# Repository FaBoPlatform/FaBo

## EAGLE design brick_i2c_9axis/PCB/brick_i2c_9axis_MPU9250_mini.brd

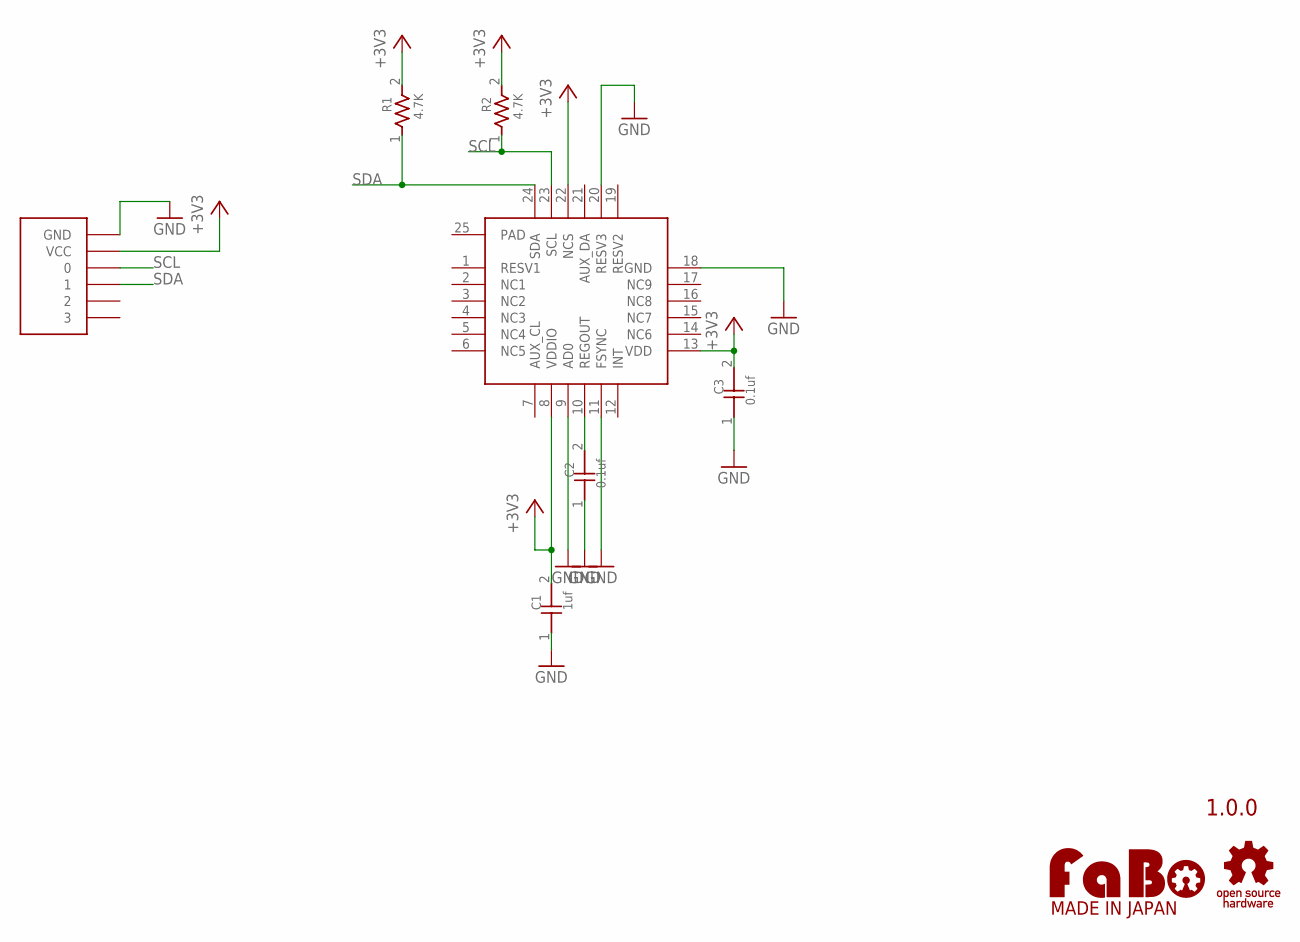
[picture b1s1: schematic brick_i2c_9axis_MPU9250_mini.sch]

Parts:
C1: 1uf; 0603
C2, C3: 0.1uf; 0603
R1, R2: 4.7K; 0603
U$1: INVENSENSE-MPU9250; LGA-24
U$3: LOGO_OSHW-S_BOTTOM; LOGO_OSHW_S_BOTTOM
U$4: FABO-NANO
U$5: LOGO_FABO-S_BOTTOM; LOGO_FABO_S_BOTTOM

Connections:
+3V3: C1.2, C3.2, R1.2, R2.2, U$1.8 (VDDIO), U$1.13 (VDD), U$1.22 (NCS), U$4.VCC
GND: C1.1, C2.1, C3.1, U$1.9 (AD0), U$1.11 (FSYNC), U$1.18 (GND), U$1.20 (RESV3), U$4.GND
unnamed: C2.2, U$1.10 (REGOUT)
SCL: R2.1, U$1.23 (SCL), U$4.0
SDA: R1.1, U$1.24 (SDA), U$4.1

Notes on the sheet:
1.0.0

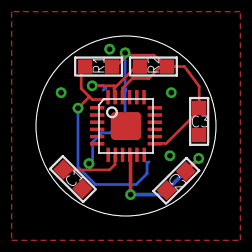
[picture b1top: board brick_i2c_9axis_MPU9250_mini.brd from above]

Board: 2 copper layers, 10.0 x 10.0 mm, 9 parts (0 on the bottom side), 5 nets.

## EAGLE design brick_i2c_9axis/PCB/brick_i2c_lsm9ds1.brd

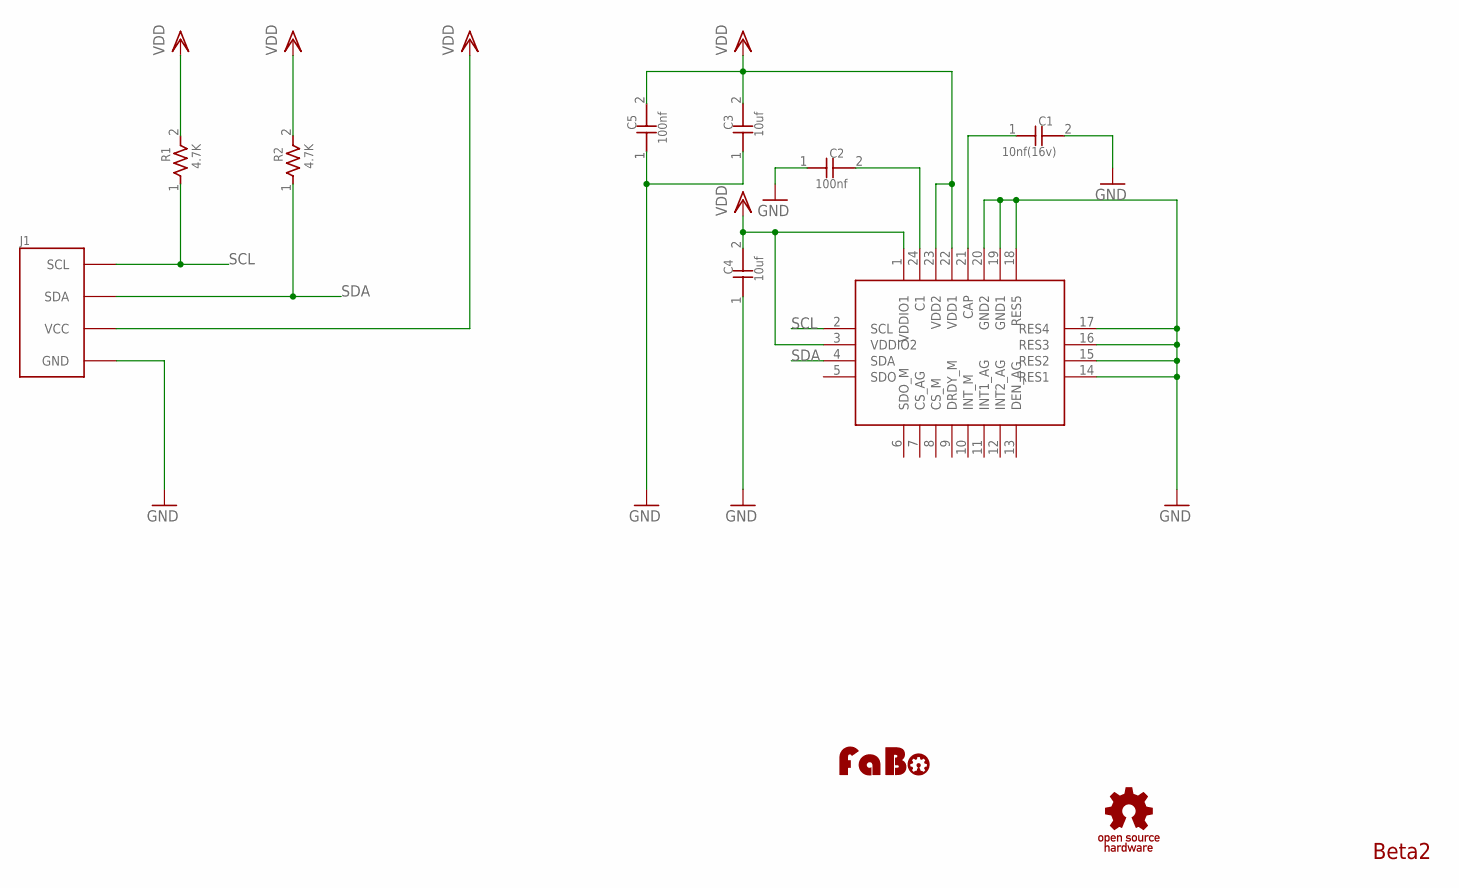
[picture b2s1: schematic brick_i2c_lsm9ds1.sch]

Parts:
C1: 10nf(16v); 0603
C2, C5: 100nf; 0603
C3, C4: 10uf; 0603
J1: BRICK_I2C
R1, R2: 4.7K; 0603
U$1: ST-LSM9DS1TR
U$3: LOGO_OSHW_T-M; LOGO_OSHW_T_M
U$4: LOGO_FABO-M; LOGO_FABO_M

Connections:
GND: C1.2, C2.1, C3.1, C4.1, C5.1, J1.GND, U$1.14 (RES1), U$1.15 (RES2), U$1.16 (RES3), U$1.17 (RES4), U$1.18 (RES5), U$1.19 (GND1), U$1.20 (GND2)
unnamed: C1.1, U$1.21 (CAP)
unnamed: C2.2, U$1.24 (C1)
SCL: J1.SCL, R1.1, U$1.2 (SCL)
SDA: J1.SDA, R2.1, U$1.4 (SDA)
VDD: C3.2, C4.2, C5.2, J1.VCC, R1.2, R2.2, U$1.1 (VDDIO1), U$1.3 (VDDIO2), U$1.22 (VDD1), U$1.23 (VDD2)

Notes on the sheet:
Beta2

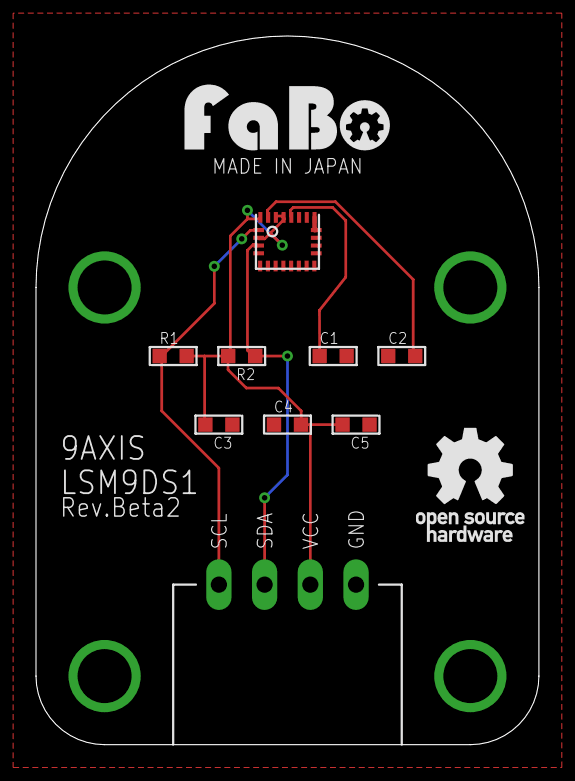
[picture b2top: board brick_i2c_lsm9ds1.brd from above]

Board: 2 copper layers, 27.9 x 39.4 mm, 11 parts (0 on the bottom side), 6 nets.

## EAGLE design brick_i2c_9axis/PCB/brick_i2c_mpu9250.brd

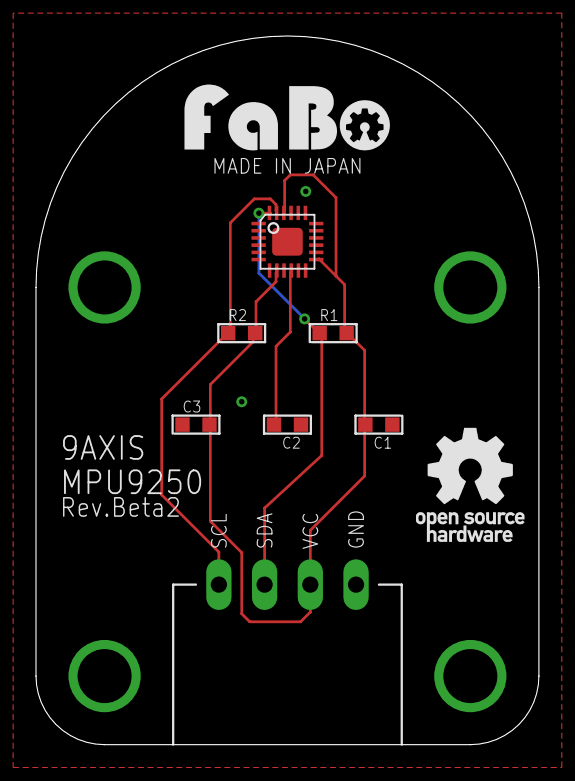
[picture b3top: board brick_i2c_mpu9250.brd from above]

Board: 2 copper layers, 27.9 x 39.4 mm, 9 parts (0 on the bottom side), 5 nets.

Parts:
C1: 1uf; 0603
C2, C3: 0.1uf; 0603
J1: BRICK_I2C
R1, R2: 4.7K; 0603
U$1: INVENSENSE-MPU9250; LGA-24
U$3: LOGO_FABO_M
U$5: LOGO_OSHW_T_M

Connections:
+3V3: C1.2, C3.2, J1.VCC, R1.2, R2.2, U$1.8, U$1.13, U$1.22
GND: C1.1, C2.1, C3.1, J1.GND, U$1.9, U$1.11, U$1.18, U$1.20
unnamed: C2.2, U$1.10
SCL: J1.SCL, R2.1, U$1.23
SDA: J1.SDA, R1.1, U$1.24

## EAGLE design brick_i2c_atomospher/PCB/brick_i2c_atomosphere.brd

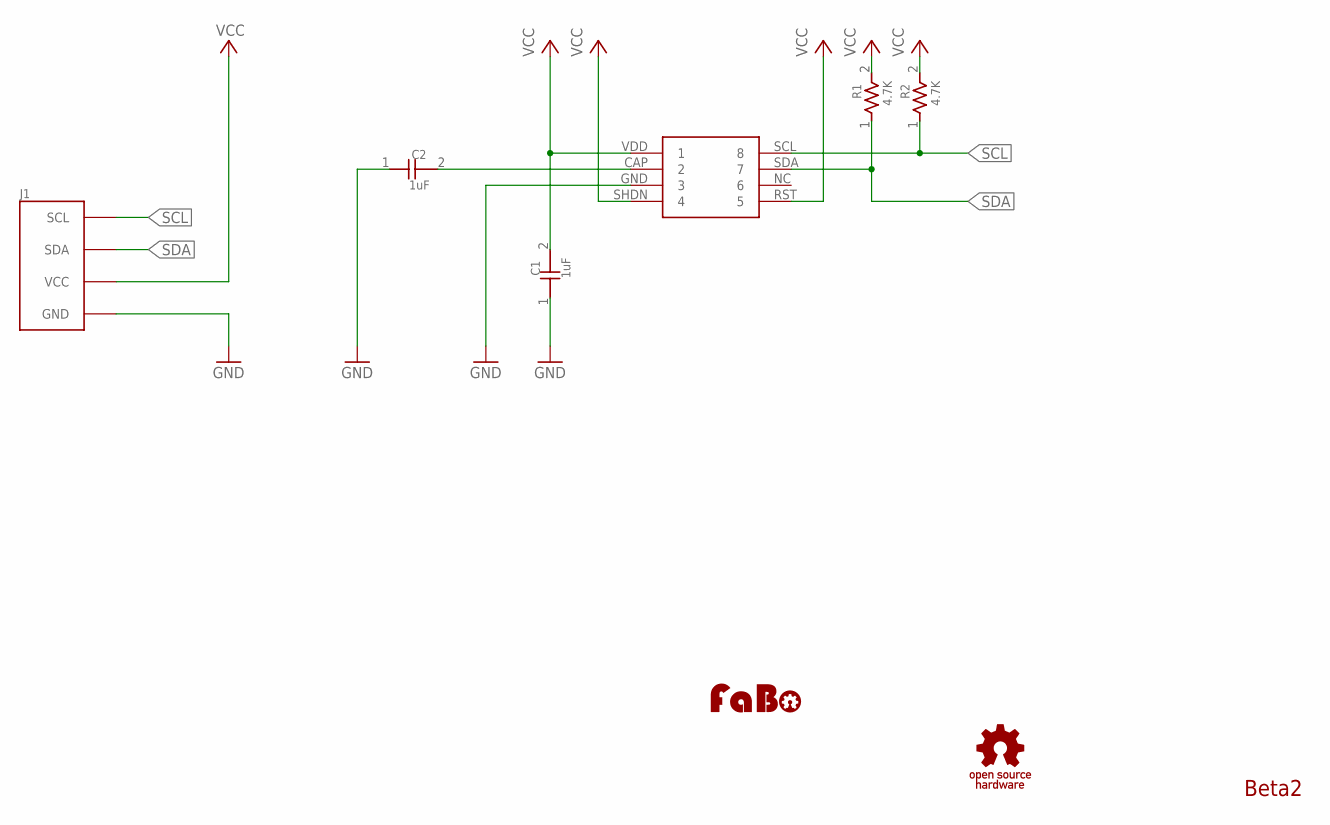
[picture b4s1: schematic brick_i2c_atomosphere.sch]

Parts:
C1, C2: 1uF; 0603
J1: BRICK_I2C
R1, R2: 4.7K; 0603
U$2: I2C-MPL115A2; I2C-MLP115A2
U$3: LOGO_FABO-M; LOGO_FABO_M
U$5: LOGO_OSHW_T-M; LOGO_OSHW_T_M

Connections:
GND: C1.1, C2.1, J1.GND, U$2.GND (3)
unnamed: C2.2, U$2.CAP (2)
SCL: J1.SCL, R2.1, U$2.SCL (8)
SDA: J1.SDA, R1.1, U$2.SDA (7)
VCC: C1.2, J1.VCC, R1.2, R2.2, U$2.RST (5), U$2.SHDN (4), U$2.VDD (1)

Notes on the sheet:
Beta2

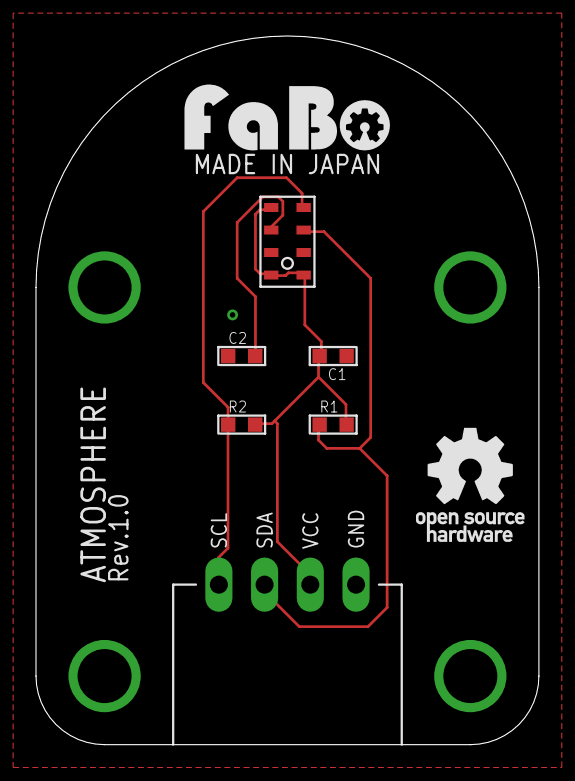
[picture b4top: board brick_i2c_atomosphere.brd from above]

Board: 2 copper layers, 27.9 x 39.4 mm, 8 parts (0 on the bottom side), 5 nets.

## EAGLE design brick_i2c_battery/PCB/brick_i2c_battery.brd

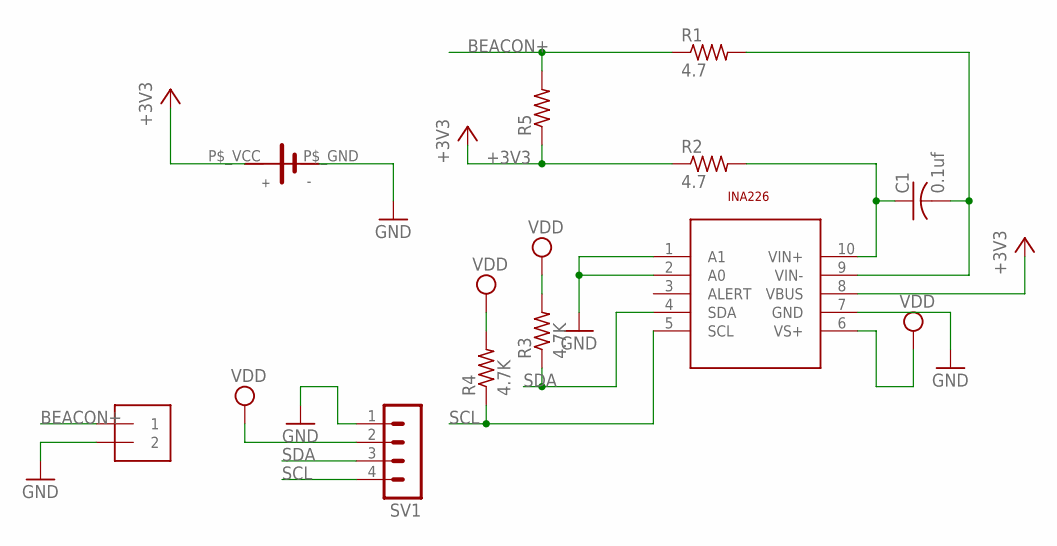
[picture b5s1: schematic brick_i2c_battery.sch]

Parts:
C1: 0.1uf; C0603
INA1: TI-INA226
J1: 1X2-3.5MM
R1, R2: 4.7; R0603
R3, R4: 4.7K; R0603
R5: R-US_R6332; R6332
SV1: MA04-1
U$2: SMTU2450

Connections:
+3V3: INA1.8 (VBUS), R2.1, R5.1, U$2.P$_VCC
BEACON+: J1.1, R1.1, R5.2
GND: INA1.1 (A1), INA1.2 (A0), INA1.7 (GND), J1.2, SV1.1, U$2.P$_GND
unnamed: C1.1, INA1.10 (VIN+), R2.2
unnamed: C1.2, INA1.9 (VIN-), R1.2
SCL: INA1.5 (SCL), R4.1, SV1.4
SDA: INA1.4 (SDA), R3.1, SV1.3
VDD: INA1.6 (VS+), R3.2, R4.2, SV1.2

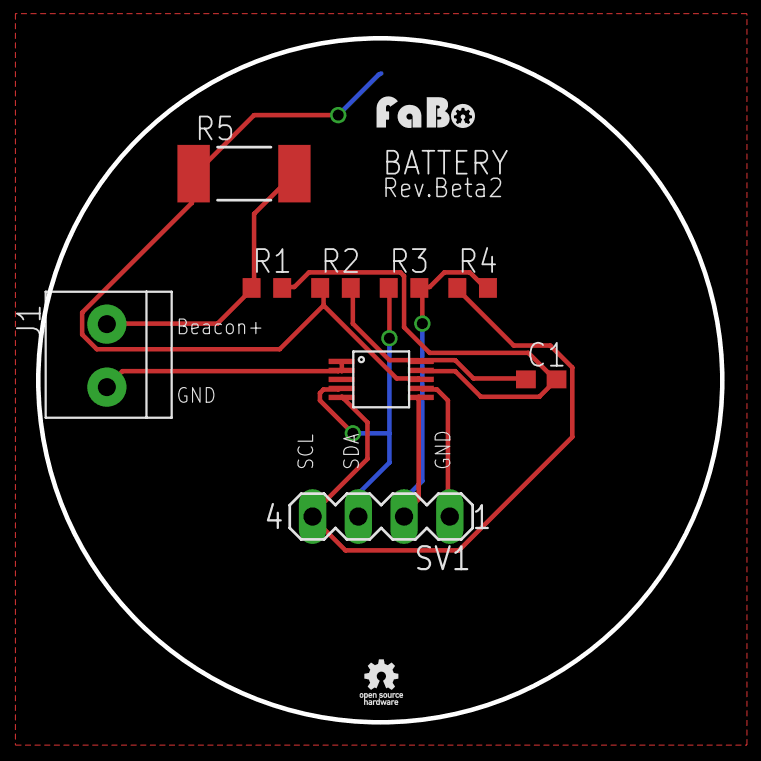
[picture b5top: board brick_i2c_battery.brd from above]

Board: 2 copper layers, 38.0 x 38.0 mm, 12 parts (0 on the bottom side), 8 nets.

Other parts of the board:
U$3: LOGO_FABO_S
U$4: LOGO_OSHW_T_S

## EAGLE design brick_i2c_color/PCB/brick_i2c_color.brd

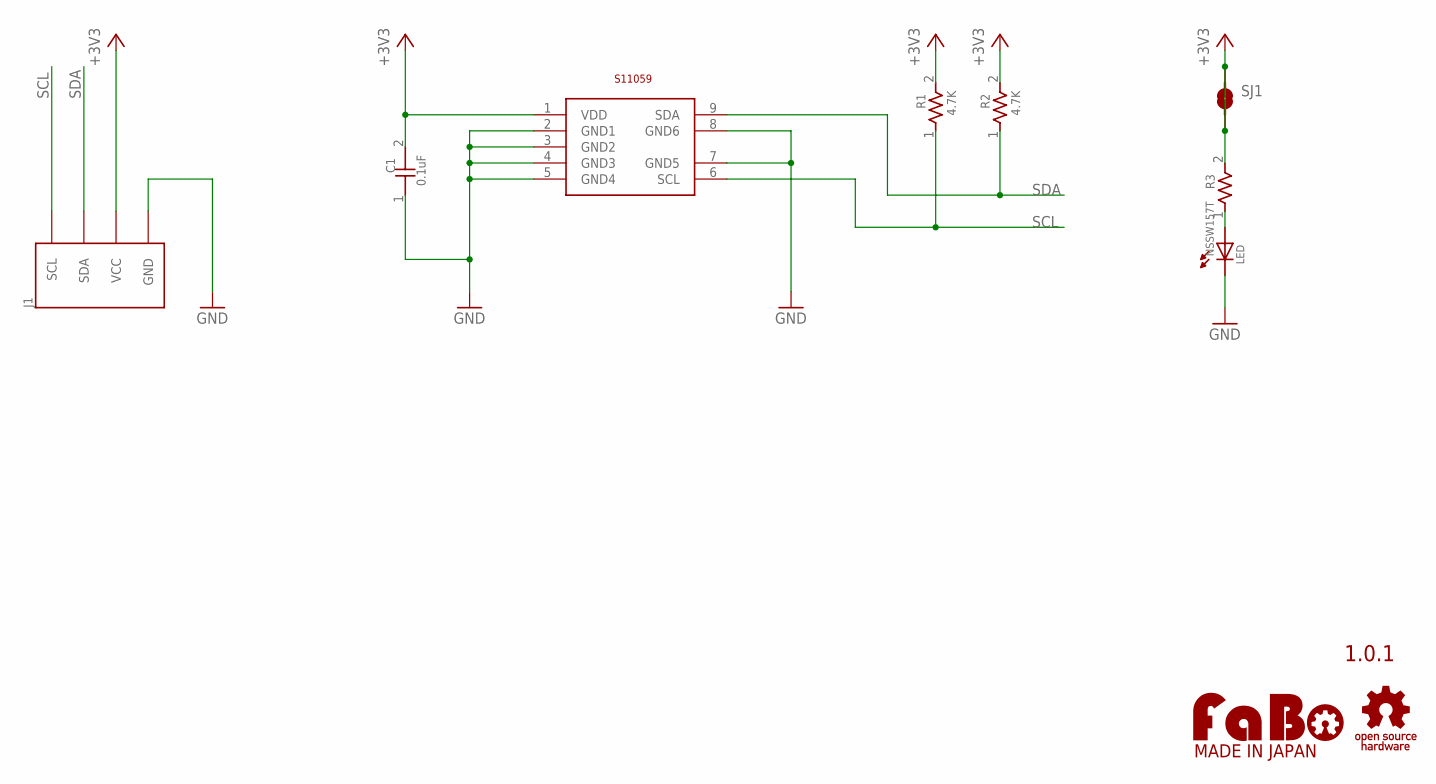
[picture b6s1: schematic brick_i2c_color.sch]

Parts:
C1: 0.1uF; 0603
J1: BRICK_I2C
LED: NSSW157T
R1, R2: 4.7K; 0603
R3: RESISTOR0603; 0603
S1: HAMAMATSU-S11059
SJ1: SMD-JUMPER-2
U$2: LOGO_OSHW_T-M; LOGO_OSHW_T_M
U$3: LOGO_FABO-M; LOGO_FABO_M

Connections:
+3V3: C1.2, J1.VCC, R1.2, R2.2, R3.2, S1.1 (VDD), SJ1.1, SJ1.2
GND: C1.1, J1.GND, LED.CATHODE1 (CATHODE), LED.CATHODE2 (CATHODE), S1.2 (GND1), S1.3 (GND2), S1.4 (GND3), S1.5 (GND4), S1.7 (GND5), S1.8 (GND6)
unnamed: LED.ANODE1 (ANODE), LED.ANODE2 (ANODE), R3.1
SCL: J1.SCL, R1.1, S1.6 (SCL)
SDA: J1.SDA, R2.1, S1.9 (SDA)

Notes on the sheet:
1.0.1

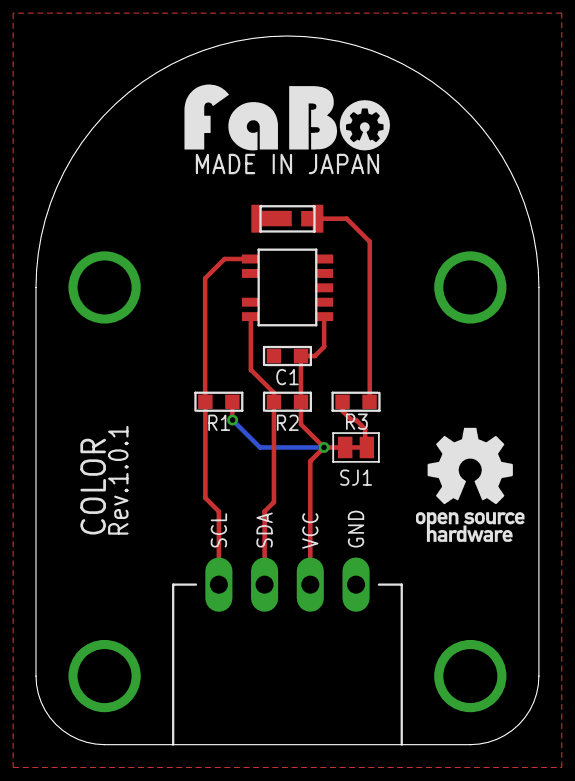
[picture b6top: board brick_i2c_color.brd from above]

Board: 2 copper layers, 27.9 x 39.4 mm, 10 parts (0 on the bottom side), 5 nets.

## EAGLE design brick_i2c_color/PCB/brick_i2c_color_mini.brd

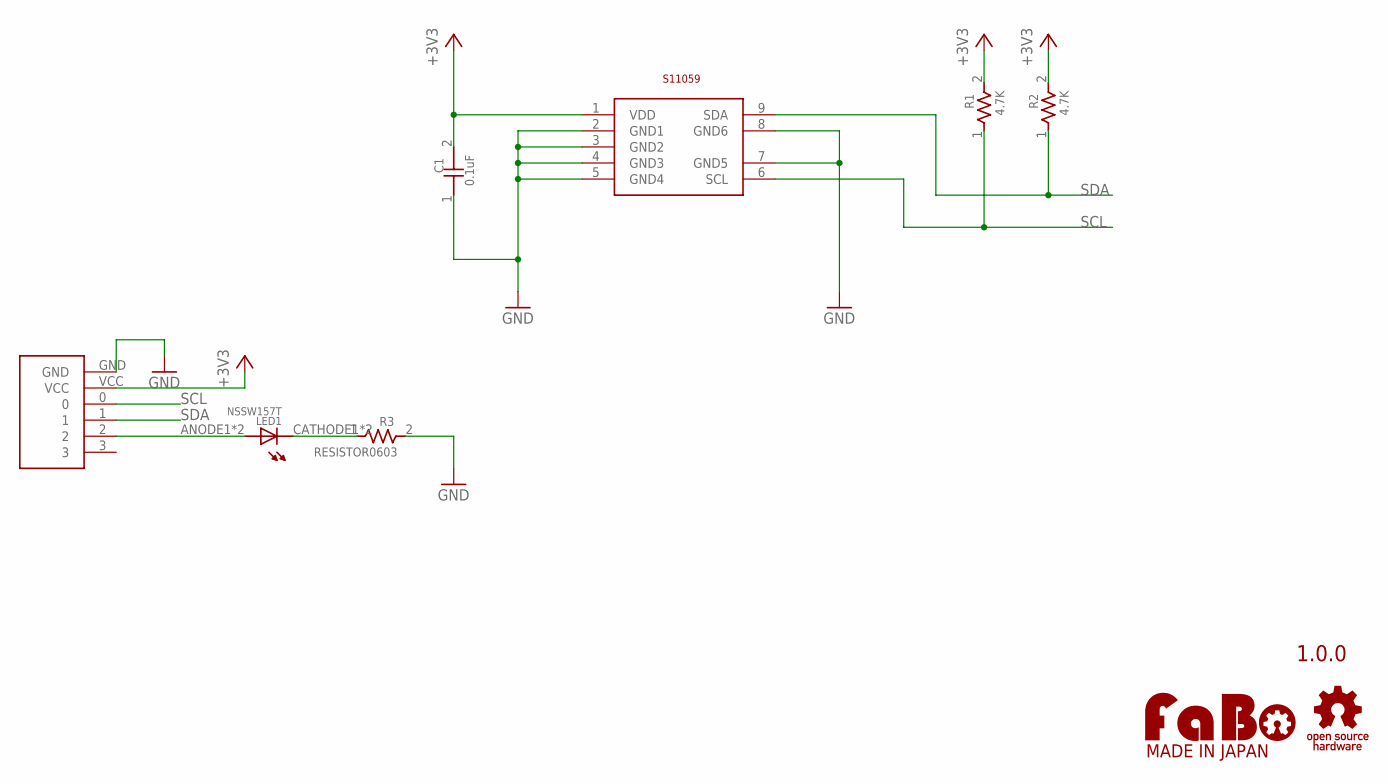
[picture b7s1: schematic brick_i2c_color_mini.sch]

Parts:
C1: 0.1uF; 0603
LED1: NSSW157T
R1, R2: 4.7K; 0603
R3: RESISTOR0603; 0603
S1: HAMAMATSU-S11059
U$2: LOGO_FABO-S_BOTTOM; LOGO_FABO_S_BOTTOM
U$3: LOGO_OSHW-S_BOTTOM; LOGO_OSHW_S_BOTTOM
U$4: FABO-NANO

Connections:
+3V3: C1.2, R1.2, R2.2, S1.1 (VDD), U$4.VCC
GND: C1.1, R3.2, S1.2 (GND1), S1.3 (GND2), S1.4 (GND3), S1.5 (GND4), S1.7 (GND5), S1.8 (GND6), U$4.GND
unnamed: LED1.ANODE1 (ANODE), LED1.ANODE2 (ANODE), U$4.2
unnamed: LED1.CATHODE1 (CATHODE), LED1.CATHODE2 (CATHODE), R3.1
SCL: R1.1, S1.6 (SCL), U$4.0
SDA: R2.1, S1.9 (SDA), U$4.1

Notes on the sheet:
1.0.0

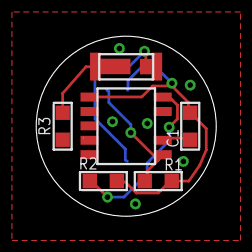
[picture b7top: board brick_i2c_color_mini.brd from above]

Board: 2 copper layers, 10.0 x 10.0 mm, 9 parts (0 on the bottom side), 6 nets.

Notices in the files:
parts and their libraries:
FaBo-etc: Released under the Creative Commons Attribution-ShareAlike 4.0 License
https://creativecommons.org/licenses/by-sa/4.0
gclue: Released under the Creative Commons
